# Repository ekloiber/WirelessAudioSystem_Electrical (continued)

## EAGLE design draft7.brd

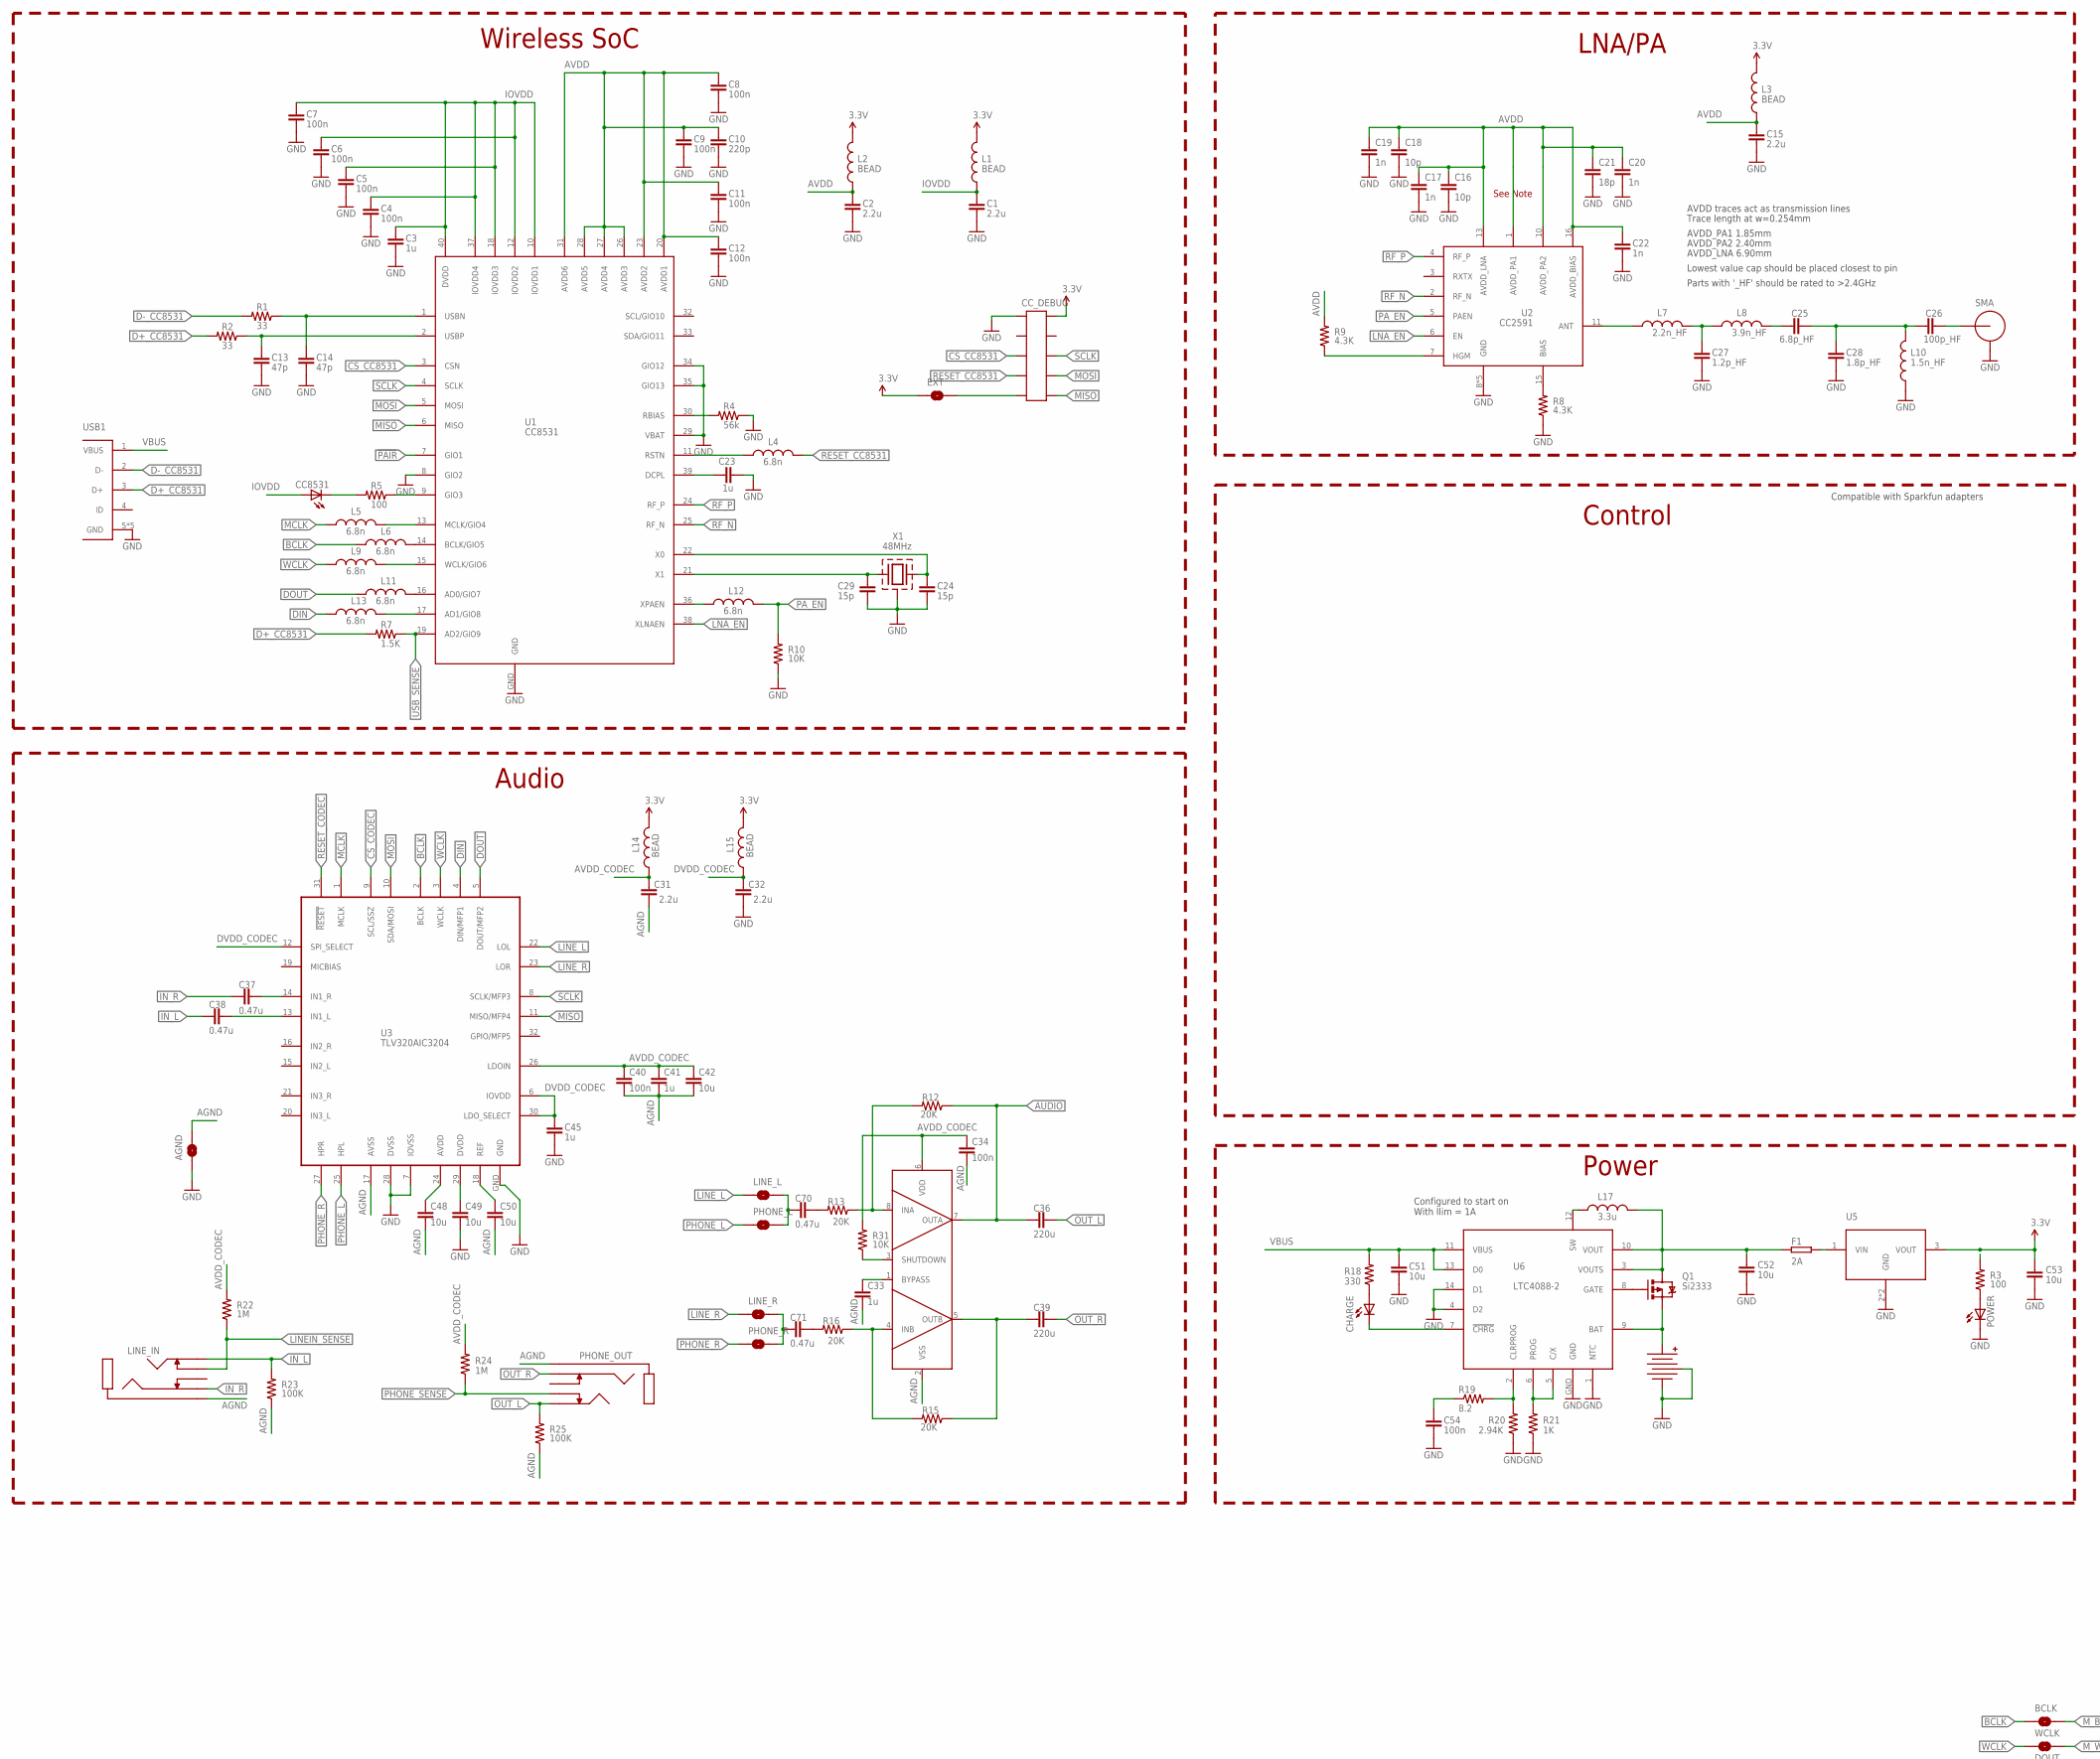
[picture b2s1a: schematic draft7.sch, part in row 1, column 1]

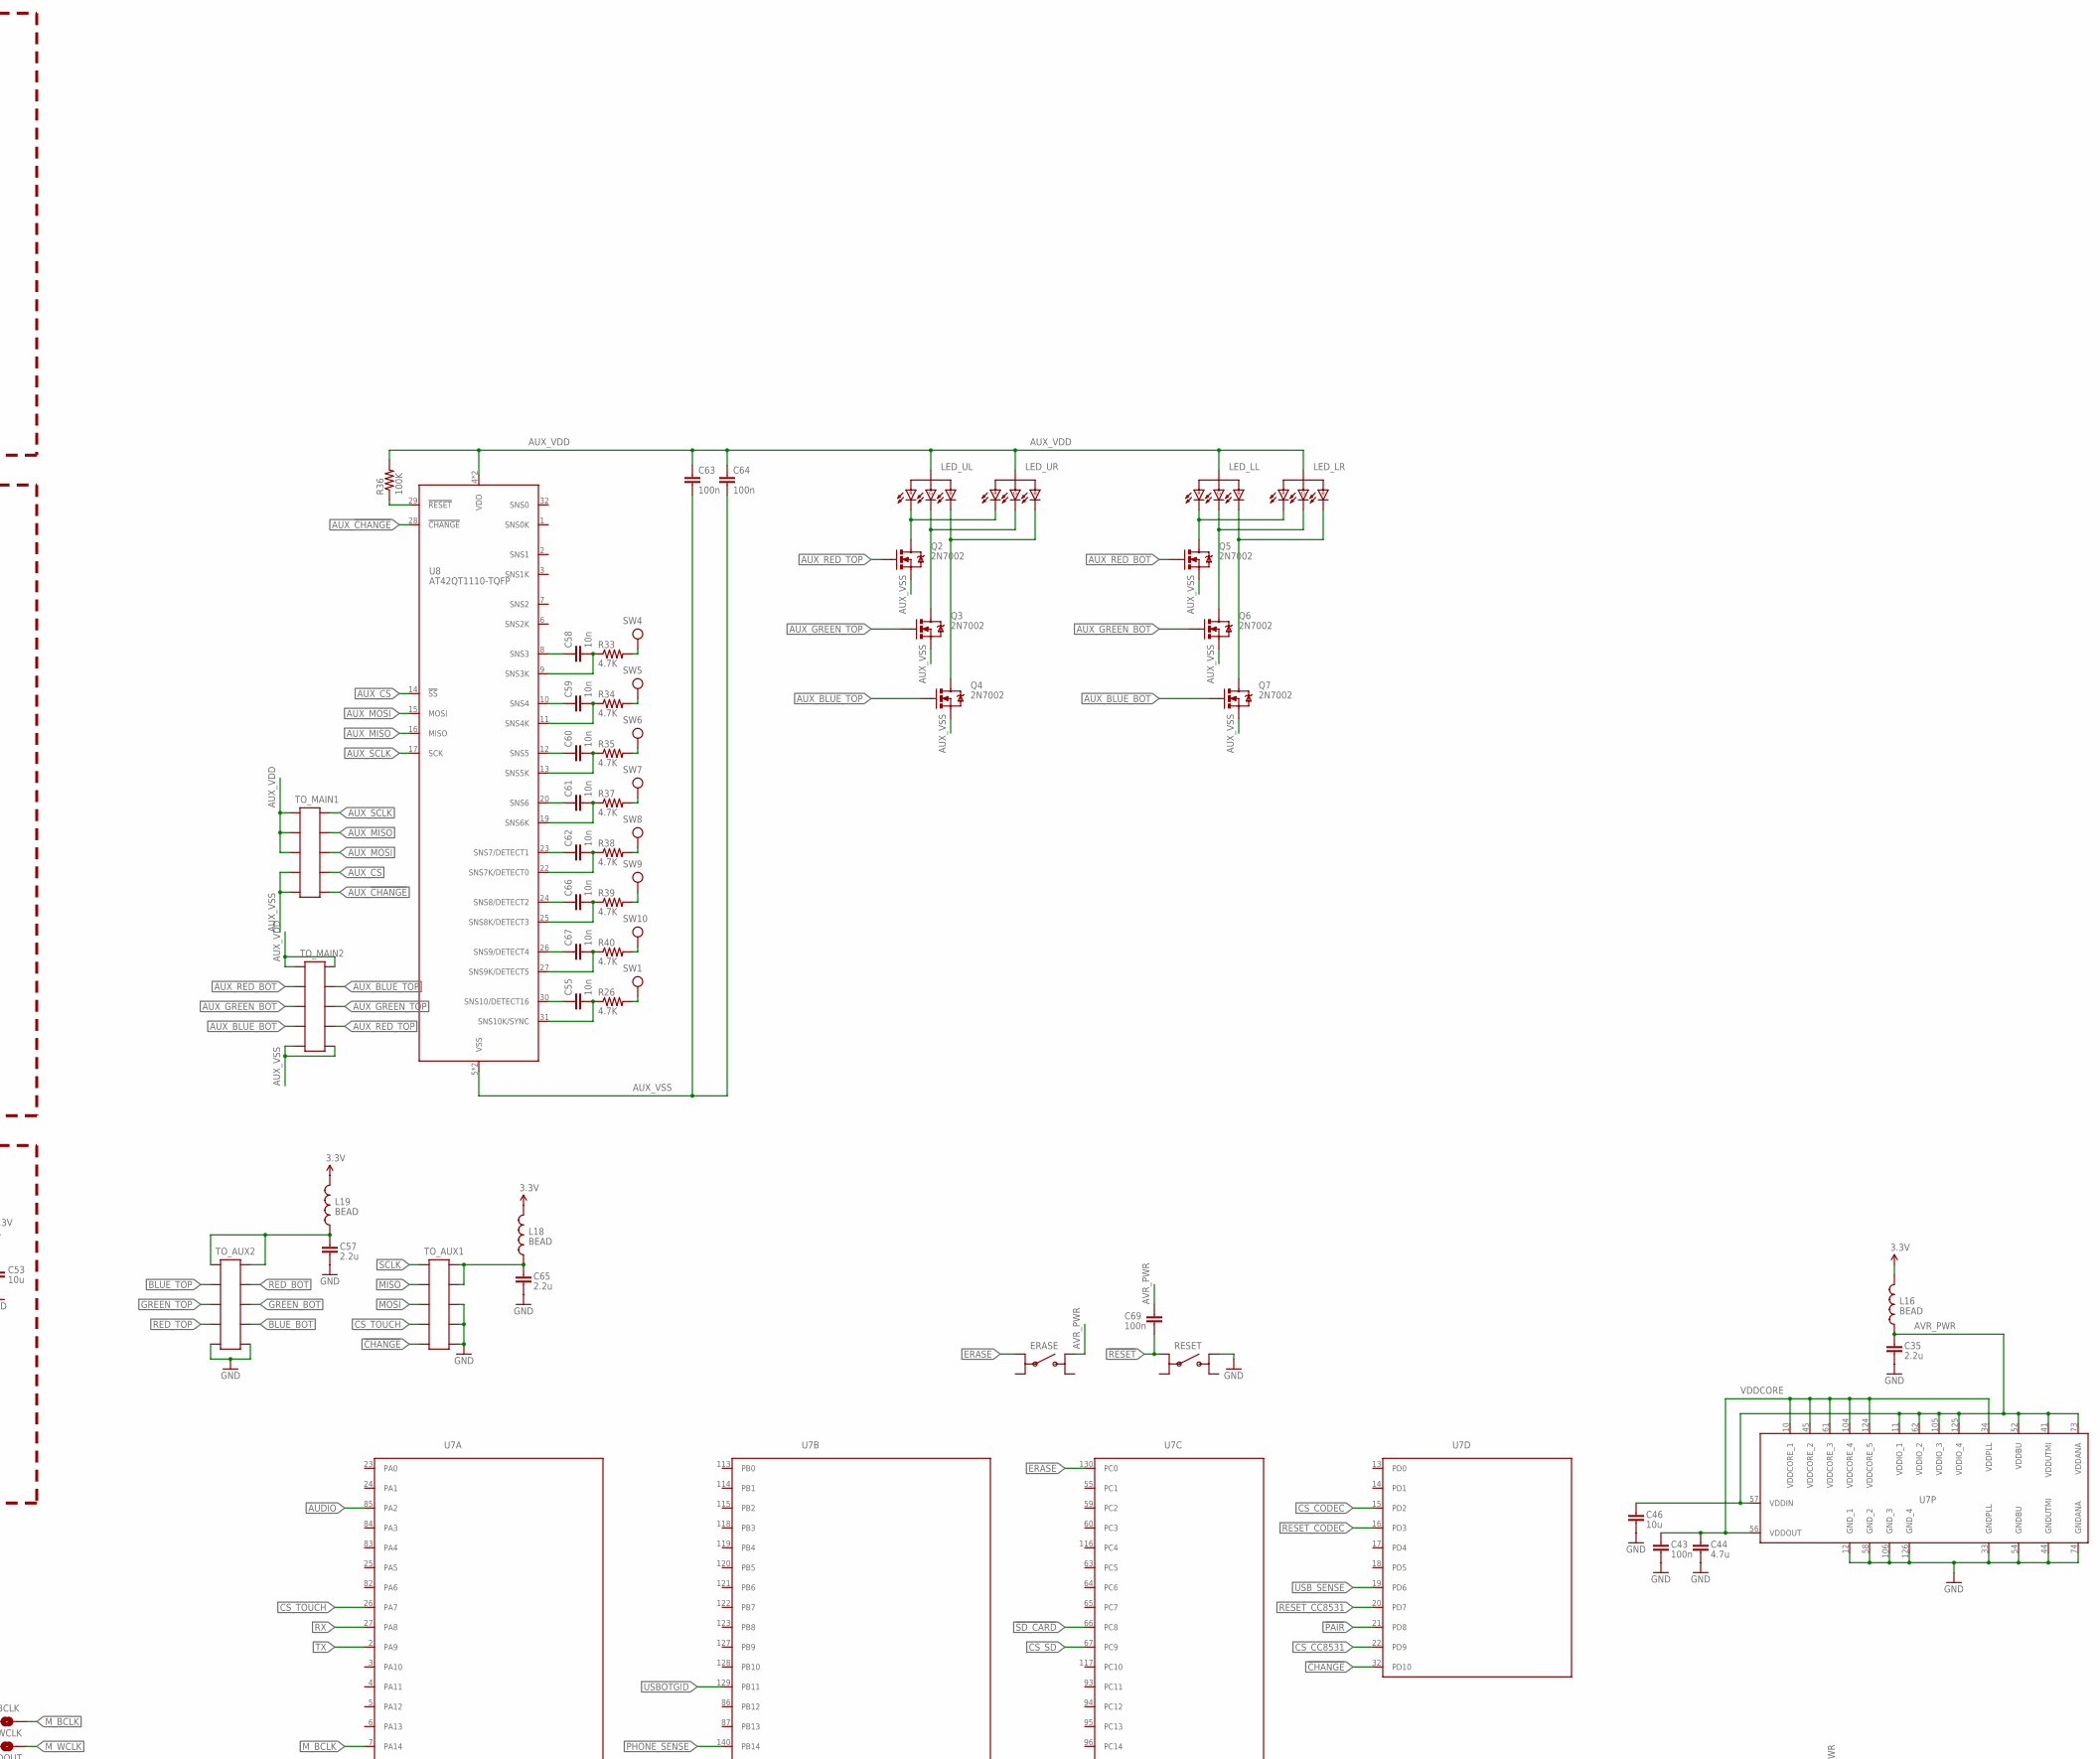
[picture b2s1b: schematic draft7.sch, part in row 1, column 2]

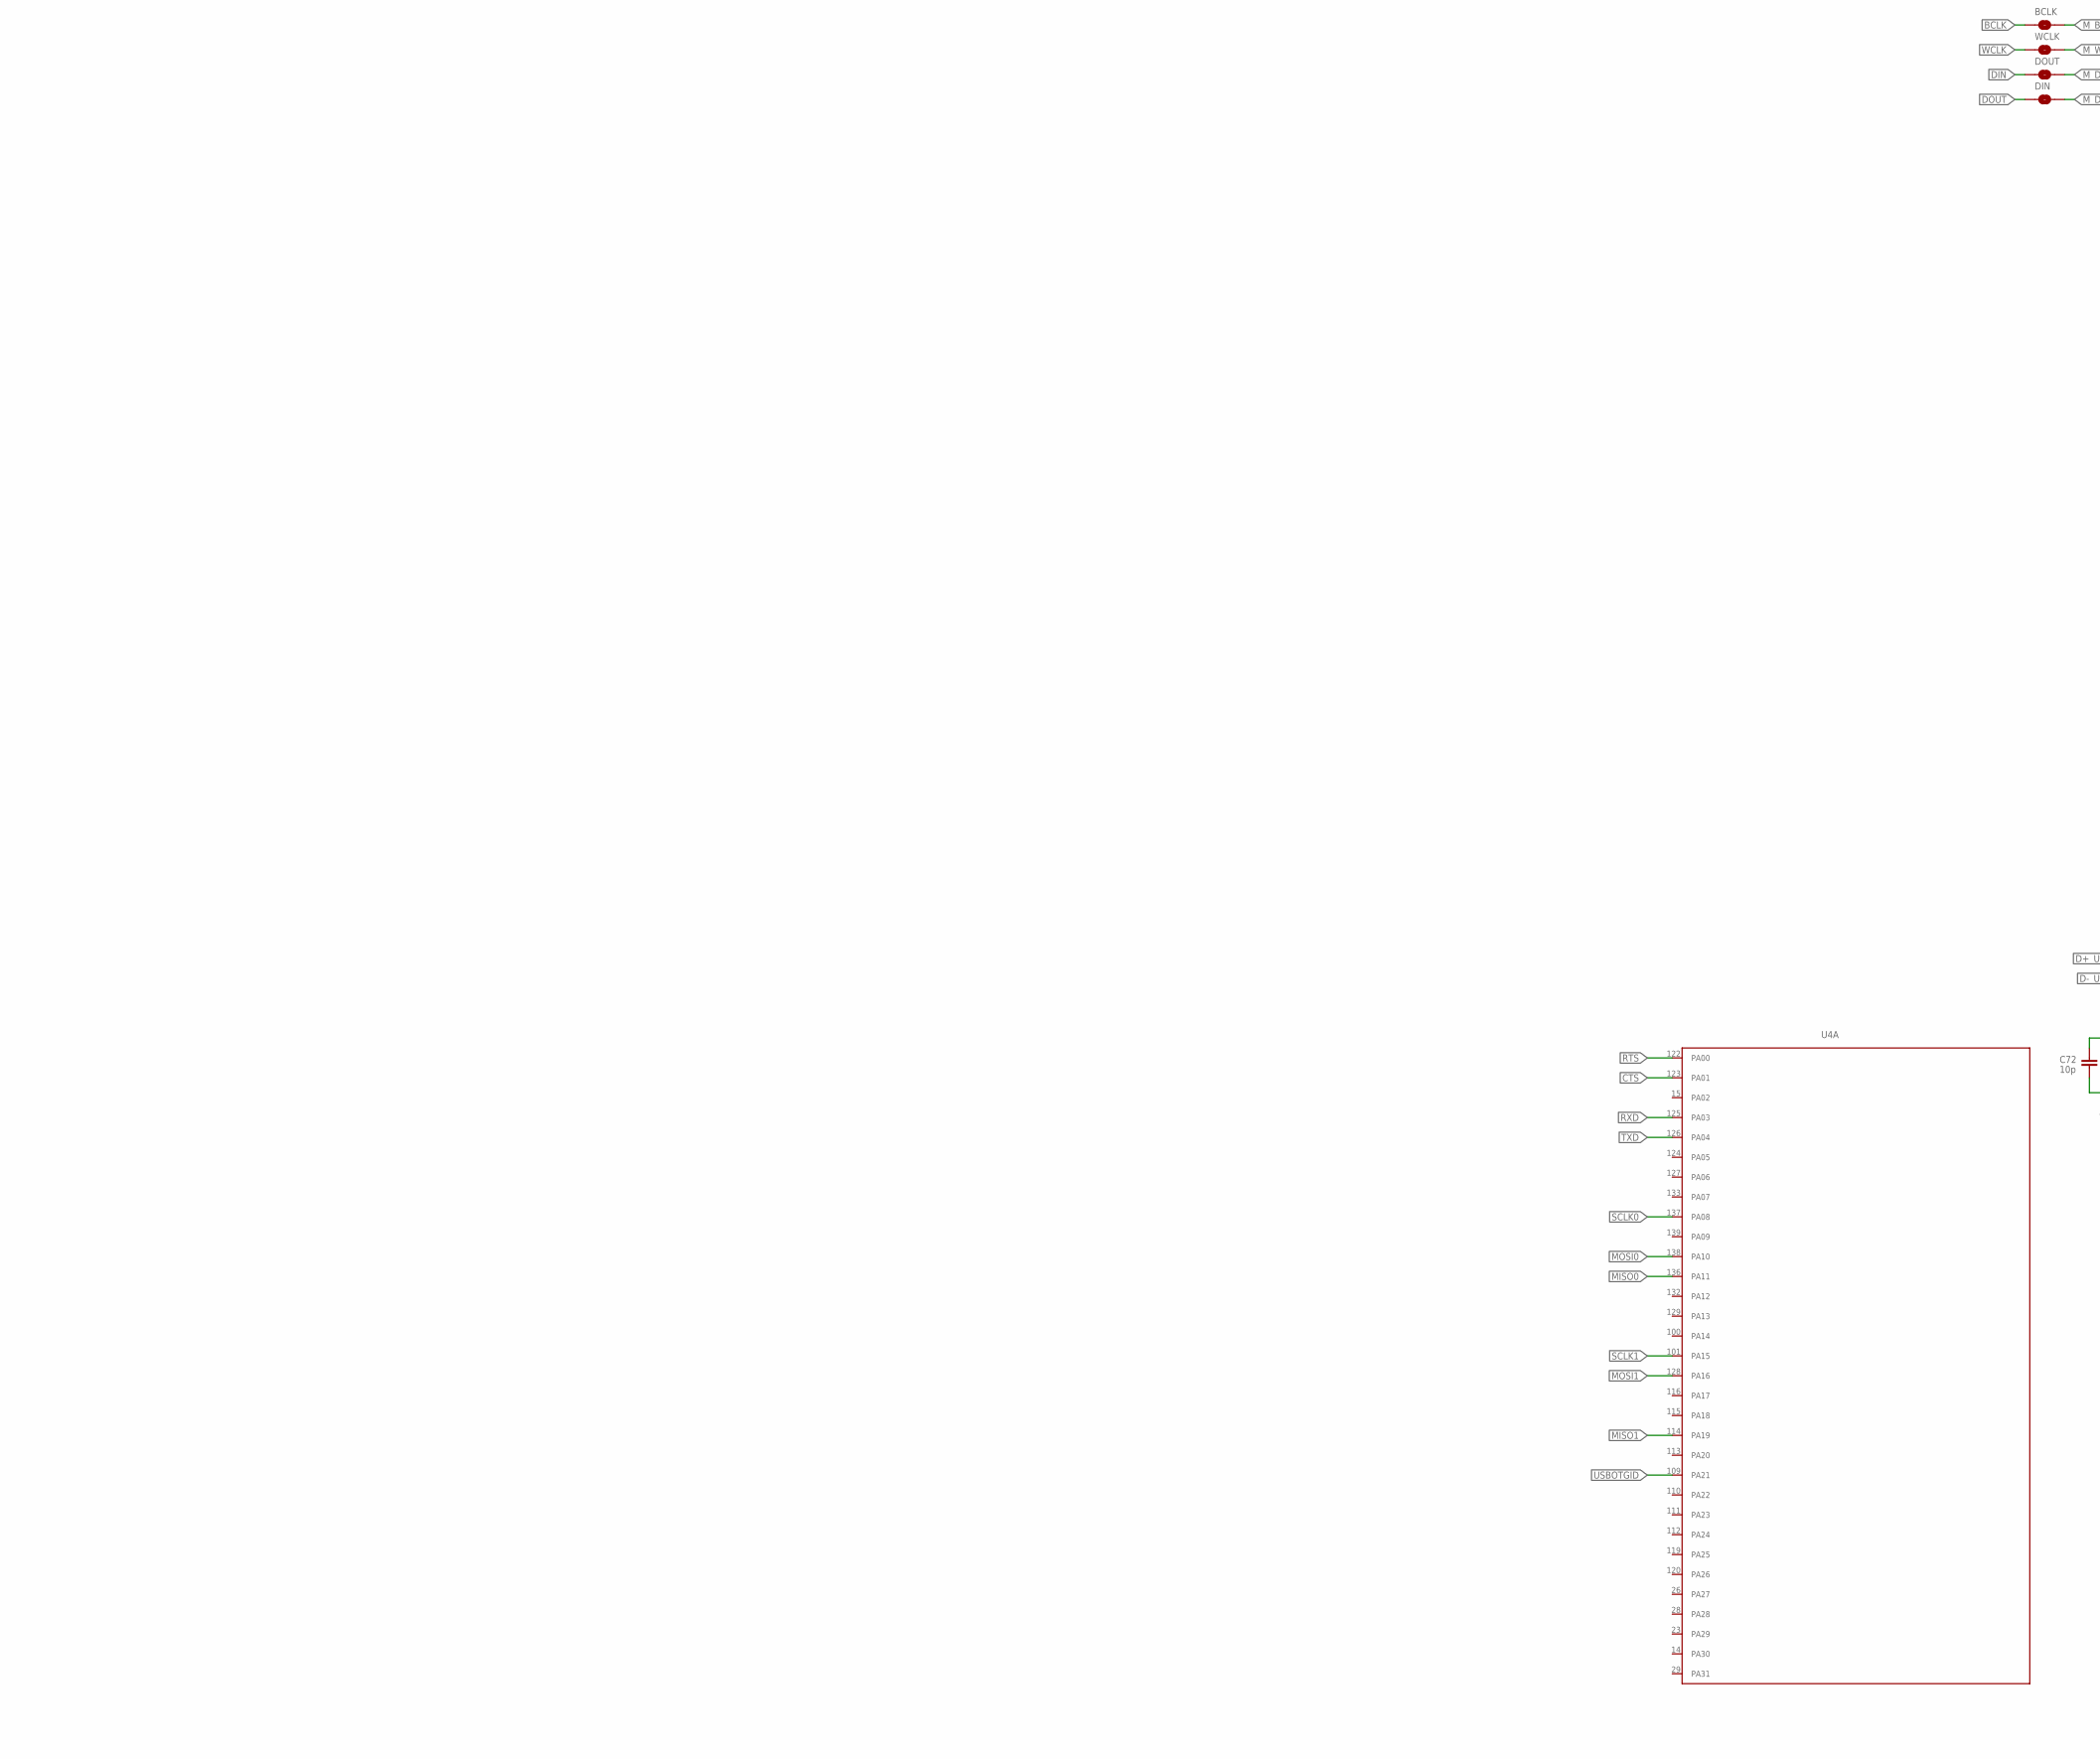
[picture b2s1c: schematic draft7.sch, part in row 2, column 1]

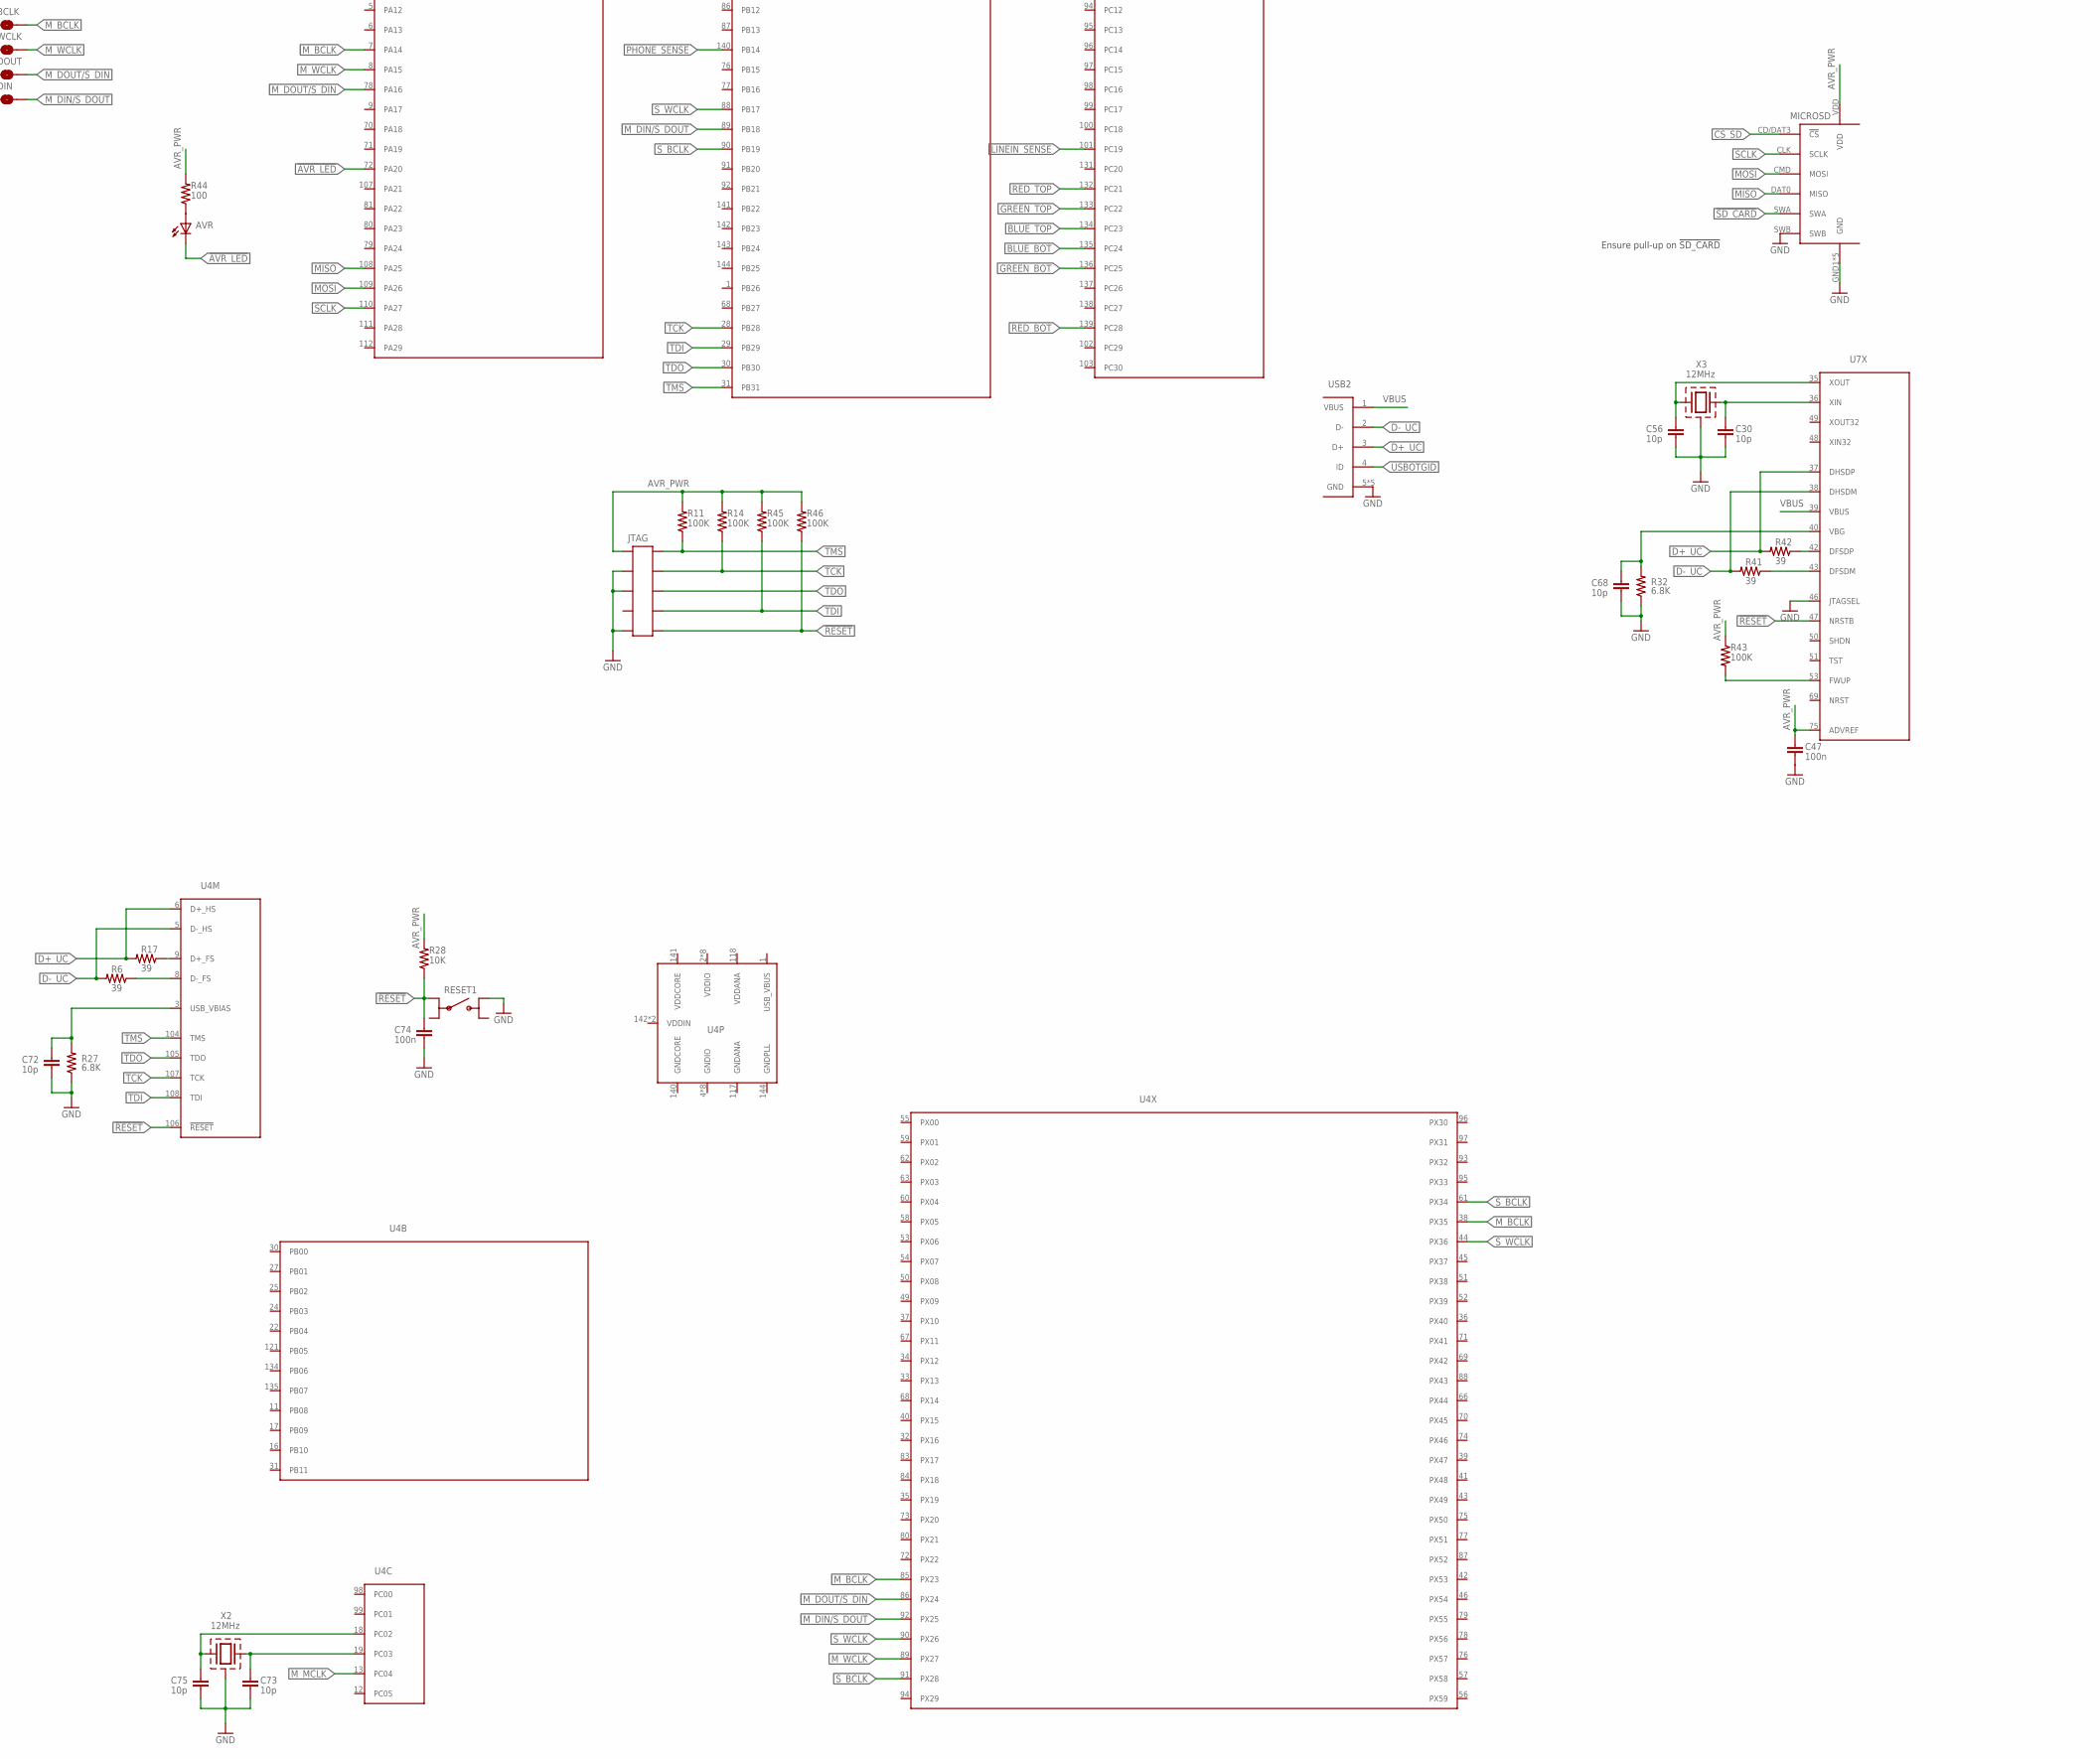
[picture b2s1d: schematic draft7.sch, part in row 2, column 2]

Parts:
AGND: SOLDERJUMPERNO; SJ_2S-NO
AVR: LED1206; LED-1206
BATTERY: BATTERY-LIPO-JST; 1775469-2
BCLK: SOLDERJUMPERNO; SJ_2S-NO
C1, C2, C15, C31, C32, C35, C57, C65: 2.2u; C0603
C3, C23, C33, C41, C45: 1u; C0603
C4, C5, C6, C7, C8, C9, C11, C12, C34, C40, C43, C47, C54, C63, C64, C69, C74: 100n; C0603
C10: 220p; C0603
C13, C14: 47p; C0603
C16, C18, C30, C56, C68, C72, C73, C75: 10p; C0603
C17, C19, C20, C22: 1n; C0603
C21: 18p; C0603
C24, C29: 15p; C0603
C25: 6.8p_HF; C0603
C26: 100p_HF; C0603
C27: 1.2p_HF; C0603
C28: 1.8p_HF; C0603
C36, C39: 220u; C1210
C37, C38, C70, C71: 0.47u; C0603
C42, C46, C48, C49, C50, C51, C52, C53: 10u; C0603
C44: 4.7u; C0603
C55, C58, C59, C60, C61, C62, C66, C67: 10n; C0603
CC8531: LED1206; LED-1206
CC_DEBUG: HEADER-10P-SMD-MALE2; HEADER-10P-1.27MM
CHARGE: LED1206; LED-1206
DIN: SOLDERJUMPERNO; SJ_2S-NO
DOUT: SOLDERJUMPERNO; SJ_2S-NO
ERASE: TACT_SWITCH-PTS-525; PTS-525
EXT: SOLDERJUMPERNO; SJ_2S-NO
F1: 2A; 1210
JTAG: HEADER-10P-SMD-MALE2; HEADER-10P-1.27MM
L1, L2, L3, L14, L15, L16, L18, L19: BEAD; 0603
L4, L5, L6, L9, L11, L12, L13: 6.8n; 0603
L7: 2.2n_HF; 0603
L8: 3.9n_HF; 0603
L10: 1.5n_HF; 0603
L17: 3.3u; IFSC-1111AB-01
LED_LL: LED_RGB; PLCC-4
LED_LR: LED_RGB; PLCC-4
LED_UL: LED_RGB; PLCC-4
LED_UR: LED_RGB; PLCC-4
LINE_IN: PHONE_SW-STX-35332-5N; STX-35332-5N
LINE_L: SOLDERJUMPERNO; SJ_2S-NO
LINE_R: SOLDERJUMPERNO; SJ_2S-NO
MICROSD: MICROSD104031-0811; MOLEX_104031-0811
PHONE_L: SOLDERJUMPERNO; SJ_2S-NO
PHONE_OUT: PHONE_SW-STX-35332-5N; STX-35332-5N
PHONE_R: SOLDERJUMPERNO; SJ_2S-NO
POWER: LED1206; LED-1206
Q1: Si2333; SOT23-3
Q2, Q3, Q4, Q5, Q6, Q7: 2N7002; SOT23-3
R1, R2: 33; R0603
R3, R5, R44: 100; R0603
R4: 56k; R0603
R6, R17, R41, R42: 39; R0603
R7: 1.5K; R0603
R8, R9: 4.3K; R0603
R10, R28, R31: 10K; R0603
R11, R14, R23, R25, R36, R43, R45, R46: 100K; R0603
R12, R13, R15, R16: 20K; R0603
R18: 330; R0603
R19: 8.2; R0603
R20: 2.94K; R0603
R21: 1K; R0603
R22, R24: 1M; R0603
R26, R33, R34, R35, R37, R38, R39, R40: 4.7K; R0603
R27, R32: 6.8K; R0603
RESET, RESET1: TACT_SWITCH-PTS-525; PTS-525
SMA: SMA-REVSMA-0.62; CONREVSMA003.062
SW1, SW4, SW5, SW6, SW7, SW8, SW9, SW10: TOUCH_PAD-CIRCLE-15MM; TOUCH-CIRCLE-15MM
TO_AUX1, TO_AUX2: HEADER-10P-SMD-2MM-FEMALE; M22-63405
TO_MAIN1, TO_MAIN2: HEADER-10P-SMD-2MM-MALE; M22-53205
U1: CC8531; S-PVQFN-N40
U2: CC2591; S-PVQFN-N16
U3: TLV320AIC3204; S-PVQFN-N32
U4: AT32UC3A3-LQFP-144; LQFP-144
U5: MCP1826-SOT223; SOT-223
U6: LTC4088-2; DFN-14
U7: ATSAM3X8E_ALT-LQFP-144; LQFP-144
U8: AT42QT1110-TQFP; S-PQFP-N32
U9: LM4881; SO08
USB1, USB2: USB_MICRO_AB
WCLK: SOLDERJUMPERNO; SJ_2S-NO
X1: 48MHz; ABM3C
X2, X3: 12MHz; ABM8G

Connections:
3.3V: C53.1, CC_DEBUG.2, EXT.1, L1.2, L2.2, L3.2, L14.2, L15.2, L16.2, L18.2, L19.2, R3.2, U5.3 (VOUT)
!AVR_LED: AVR.C, U7.72 (PA20)
!CHANGE: TO_AUX1.9, U7.32 (PD10)
!PAIR: U1.7 (GIO1), U7.21 (PD8)
!RESET: C69.2, C74.1, JTAG.10, R28.1, R46.1, RESET.1, RESET1.1, U4.106 (!RESET), U7.47 (NRSTB)
!SD_CARD: MICROSD.SWA, U7.66 (PC8)
AGND: AGND.2, C31.2, C33.2, C34.2, C40.2, C41.2, C42.2, C48.2, C50.2, LINE_IN.5 (GND), PHONE_OUT.5 (GND), R23.1, R25.1, U3.17 (AVSS), U9.2 (VSS)
AUDIO: C36.1, R12.1, U7.85 (PA2), U9.7 (OUTA)
AUX_!CHANGE: TO_MAIN1.10, U8.28 (!CHANGE)
AUX_BLUE_BOT: Q7.1 (G), TO_MAIN2.7
AUX_BLUE_TOP: Q4.1 (G), TO_MAIN2.4
AUX_CS: TO_MAIN1.8, U8.14 (!SS)
AUX_GREEN_BOT: Q6.1 (G), TO_MAIN2.5
AUX_GREEN_TOP: Q3.1 (G), TO_MAIN2.6
AUX_MISO: TO_MAIN1.4, U8.16 (MISO)
AUX_MOSI: TO_MAIN1.6, U8.15 (MOSI)
AUX_RED_BOT: Q5.1 (G), TO_MAIN2.3
AUX_RED_TOP: Q2.1 (G), TO_MAIN2.8
AUX_SCLK: TO_MAIN1.2, U8.17 (SCK)
AUX_VDD: C63.1, C64.1, LED_LL.2 (A), LED_LL.2-2 (A), LED_LR.2 (A), LED_LR.2-2 (A), LED_UL.2 (A), LED_UL.2-2 (A), LED_UR.2 (A), LED_UR.2-2 (A), R36.2, TO_MAIN1.1, TO_MAIN1.3, TO_MAIN1.5, TO_MAIN2.1, TO_MAIN2.2, U8.4 (VDD), U8.18 (VDD)
AUX_VSS: C63.2, C64.2, Q2.2 (S), Q3.2 (S), Q4.2 (S), Q5.2 (S), Q6.2 (S), Q7.2 (S), TO_MAIN1.7, TO_MAIN1.9, TO_MAIN2.9, TO_MAIN2.10, U8.5 (VSS), U8.21 (VSS)
AVDD: C2.1, C8.1, C9.1, C10.1, C11.1, C12.1, C15.1, C16.1, C17.1, C18.1, C19.1, C20.1, C21.1, C22.1, L2.1, L3.1, R9.2, U1.20 (AVDD1), U1.23 (AVDD2), U1.26 (AVDD3), U1.27 (AVDD4), U1.28 (AVDD5), U1.31 (AVDD6), U2.1 (AVDD_PA1), U2.10 (AVDD_PA2), U2.13 (AVDD_LNA), U2.16 (AVDD_BIAS)
AVDD_CODEC: C31.1, C34.1, C40.1, C41.1, C42.1, L14.1, R22.2, R24.2, R31.2, U3.26 (LDOIN), U9.6 (VDD)
AVR_PWR: C35.1, C46.1, C47.1, C69.1, ERASE.3, JTAG.1, L16.1, MICROSD.VDD, R11.2, R14.2, R28.2, R43.1, R44.2, R45.2, R46.2, U7.11 (VDDIO_1), U7.41 (VDDUTMI), U7.52 (VDDBU), U7.57 (VDDIN), U7.62 (VDDIO_2), U7.73 (VDDANA), U7.75 (ADVREF), U7.105 (VDDIO_3), U7.125 (VDDIO_4)
BAT: BATTERY.+, Q1.2 (S), U6.9 (BAT)
BCLK: BCLK.1, L6.1, U3.2 (BCLK)
BLUE_BOT: TO_AUX2.8, U7.135 (PC24)
BLUE_TOP: TO_AUX2.3, U7.134 (PC23)
CS_CC8531: CC_DEBUG.5, U1.3 (CSN), U7.22 (PD9)
CS_CODEC: U3.9 (SCL/SSZ), U7.15 (PD2)
CS_SD: MICROSD.CD/DAT3 (!CS), U7.67 (PC9)
CS_TOUCH: TO_AUX1.7, U7.26 (PA7)
CTS: U4.123 (PA01)
D+_CC8531: R2.2, R7.2, USB1.3 (D+)
D+_UC: R17.2, R42.2, U4.6 (D+_HS), U7.37 (DHSDP), USB2.3 (D+)
D-_CC8531: R1.2, USB1.2 (D-)
D-_UC: R6.2, R41.2, U4.5 (D-_HS), U7.38 (DHSDM), USB2.2 (D-)
DIN: DOUT.1, L13.1, U3.4 (DIN/MFP1)
DOUT: DIN.1, L11.1, U3.5 (DOUT/MFP2)
DVDD: C49.1, U3.29 (DVDD)
DVDD_CODEC: C32.1, C45.1, L15.1, U3.6 (IOVDD), U3.12 (SPI_SELECT), U3.30 (LDO_SELECT)
ERASE: ERASE.1, U7.130 (PC0)
GND: AGND.1, BATTERY.- (N), BATTERY.X1 (CASE), BATTERY.X2 (CASE), C1.2, C2.2, C3.2, C4.2, C5.2, C6.2, C7.2, C8.2, C9.2, C10.2, C11.2, C12.2, C13.2, C14.2, C15.2, C16.2, C17.2, C18.2, C19.2, C20.2, C21.2, C22.2, C23.2, C24.2, C27.2, C28.2, C29.2, C30.2, C32.2, C35.2, C43.2, C44.2, C45.2, C46.2, C47.2, C49.2, C51.2, C52.2, C53.2, C54.2, C56.2, C57.2, C65.2, C68.2, C72.2, C73.2, C74.2, C75.2, CC_DEBUG.1, JTAG.3, JTAG.5, JTAG.9, L10.1, MICROSD.GND1 (GND), MICROSD.GND2 (GND), MICROSD.GND3 (GND), MICROSD.GND4 (GND), MICROSD.SWB, MICROSD.VSS (GND), POWER.C, R4.1, R8.1, R10.1, R20.1, R21.1, R27.1, R32.1, RESET.3, RESET1.3, SMA.GND1 (GND), SMA.GND2 (GND), SMA.GND3 (GND), SMA.GND4 (GND), TO_AUX1.6, TO_AUX1.8, TO_AUX1.10, TO_AUX2.9, TO_AUX2.10, U1.8 (GIO2), U1.29 (VBAT), U1.34 (GIO12), U1.35 (GIO13), U1.GND, U2.8 (GND), U2.9 (GND), U2.12 (GND), U2.14 (GND), U2.GND, U3.7 (IOVSS), U3.28 (DVSS), U3.GND, U5.2 (GND), U5.4 (GND), U6.1 (NTC), U6.4 (D2), U6.14 (D1), U6.GND, U7.12 (GND_1), U7.33 (GNDPLL), U7.44 (GNDUTMI), U7.46 (JTAGSEL), U7.54 (GNDBU), U7.58 (GND_2), U7.74 (GNDANA), U7.106 (GND_3), U7.126 (GND_4), USB1.5 (GND), USB1.GND1 (GND), USB1.GND2 (GND), USB1.GND3 (GND), USB1.GND4 (GND), USB2.5 (GND), USB2.GND1 (GND), USB2.GND2 (GND), USB2.GND3 (GND), USB2.GND4 (GND), X1.2 (CASE), X1.4 (CASE), X2.GND-1 (CASE), X2.GND-2 (CASE), X3.GND-1 (CASE), X3.GND-2 (CASE)
GREEN_BOT: TO_AUX2.6, U7.136 (PC25)
GREEN_TOP: TO_AUX2.5, U7.133 (PC22)
IN_L: C38.1, LINE_IN.4 (L), R23.2
IN_R: C37.1, LINE_IN.1 (R)
IOVDD: C1.1, C3.1, C4.1, C5.1, C6.1, C7.1, CC8531.A, L1.1, U1.10 (IOVDD1), U1.12 (IOVDD2), U1.18 (IOVDD3), U1.37 (IOVDD4), U1.40 (DVDD)
IOVDD1: C14.1, R1.1, U1.1 (USBN)
IOVDD2: C13.1, R2.1, U1.2 (USBP)
LINEIN_SENSE: LINE_IN.3 (L_SW), R22.1, U7.101 (PC19)
LINE_L: LINE_L.1, U3.22 (LOL)
LINE_R: LINE_R.1, U3.23 (LOR)
LNA_EN: U1.38 (XLNAEN), U2.6 (EN)
MCLK: L5.1, U3.1 (MCLK)
MISO: CC_DEBUG.10, MICROSD.DAT0 (MISO), TO_AUX1.3, U1.6 (MISO), U3.11 (MISO/MFP4), U7.108 (PA25)
MISO0: U4.136 (PA11)
MISO1: U4.114 (PA19)
MOSI: CC_DEBUG.8, MICROSD.CMD (MOSI), TO_AUX1.5, U1.5 (MOSI), U3.10 (SDA/MOSI), U7.109 (PA26)
MOSI0: U4.138 (PA10)
MOSI1: U4.128 (PA16)
M_BCLK: BCLK.2, U4.38 (PX35), U4.85 (PX23), U7.7 (PA14)
M_DIN/S_DOUT: DIN.2, U4.92 (PX25), U7.89 (PB18)
M_DOUT/S_DIN: DOUT.2, U4.86 (PX24), U7.78 (PA16)
M_MCLK: U4.13 (PC04)
M_WCLK: U4.89 (PX27), U7.8 (PA15), WCLK.2
unnamed: C29.1, U1.21 (X1), X1.1
unnamed: C24.1, U1.22 (X0), X1.3 (2)
unnamed: L4.1, U1.11 (RSTN)
unnamed: L11.2, U1.16 (AD0/GIO7)
unnamed: L6.2, U1.14 (BCLK/GIO5)
unnamed: C56.1, U7.35 (XOUT), X3.X1 (1)
unnamed: R8.2, U2.15 (BIAS)
unnamed: R9.1, U2.7 (HGM)
unnamed: C26.2, SMA.SIG
unnamed: C55.2, R26.1, U8.31 (SNS10K/SYNC)
unnamed: C55.1, U8.30 (SNS10/DETECT16)
unnamed: AVR.A, R44.1
unnamed: L7.1, U2.11 (ANT)
unnamed: C27.1, L7.2, L8.1
unnamed: C25.1, L8.2
unnamed: C25.2, C26.1, C28.1, L10.2
unnamed: C48.1, U3.24 (AVDD)
unnamed: L12.1, U1.36 (XPAEN)
unnamed: R4.2, U1.30 (RBIAS)
unnamed: C70.2, R13.2
unnamed: C23.1, U1.39 (DCPL)
unnamed: F1.2, U5.1 (VIN)
unnamed: L5.2, U1.13 (MCLK/GIO4)
unnamed: C71.2, R16.2
unnamed: L9.2, U1.15 (WCLK/GIO6)
unnamed: C33.1, U9.1 (BYPASS)
unnamed: L13.2, U1.17 (AD1/GIO8)
unnamed: R5.1, U1.9 (GIO3)
unnamed: CC8531.C, R5.2
unnamed: C58.2, R33.1, U8.9 (SNS3K)
unnamed: POWER.A, R3.1
unnamed: CHARGE.C, U6.7 (!CHRG)
unnamed: CHARGE.A, R18.1
unnamed: C37.2, U3.14 (IN1_R)
unnamed: C38.2, U3.13 (IN1_L)
unnamed: L17.1, U6.12 (SW)
unnamed: R21.2, U6.5 (C/X), U6.6 (PROG)
unnamed: R19.2, R20.2, U6.2 (CLRPROG)
unnamed: R6.1, U4.8 (D-_FS)
unnamed: C39.1, R15.1, U9.5 (OUTB)
unnamed: C59.2, R34.1, U8.11 (SNS4K)
unnamed: C60.2, R35.1, U8.13 (SNS5K)
unnamed: C70.1, LINE_L.2, PHONE_L.2
unnamed: R26.2, SW1.P$1
unnamed: C71.1, LINE_R.2, PHONE_R.2
unnamed: R17.1, U4.9 (D+_FS)
unnamed: C72.1, R27.2, U4.3 (USB_VBIAS)
unnamed: C54.1, R19.1
unnamed: C52.1, F1.1, L17.2, Q1.3 (D), U6.3 (VOUTS), U6.10 (VOUT)
unnamed: CC_DEBUG.9, EXT.2
unnamed: Q1.1 (G), U6.8 (GATE)
unnamed: C75.1, U4.18 (PC02), X2.X1 (1)
unnamed: R12.2, R13.1, U9.8 (INA)
unnamed: R15.2, R16.1, U9.4 (INB)
unnamed: R31.1, U9.3 (SHUTDOWN)
unnamed: LED_UL.1 (KR), LED_UL.1-2 (KR), LED_UR.1 (KR), LED_UR.1-2 (KR), Q2.3 (D)
unnamed: C73.1, U4.19 (PC03), X2.X2 (2)
unnamed: LED_UL.4 (KG), LED_UL.4-2 (KG), LED_UR.4 (KG), LED_UR.4-2 (KG), Q3.3 (D)
unnamed: C30.1, U7.36 (XIN), X3.X2 (2)
unnamed: C58.1, U8.8 (SNS3)
unnamed: R33.2, SW4.P$1
unnamed: C59.1, U8.10 (SNS4)
unnamed: R34.2, SW5.P$1
unnamed: C60.1, U8.12 (SNS5)
unnamed: R35.2, SW6.P$1
unnamed: C66.2, R39.1, U8.25 (SNS8K/DETECT3)
unnamed: C57.1, L19.1, TO_AUX2.1, TO_AUX2.2
unnamed: C67.2, R40.1, U8.27 (SNS9K/DETECT5)
unnamed: C66.1, U8.24 (SNS8/DETECT2)
unnamed: R39.2, SW9.P$1
unnamed: C61.2, R37.1, U8.19 (SNS6K)
unnamed: R37.2, SW7.P$1
unnamed: C62.2, R38.1, U8.22 (SNS7K/DETECT0)
unnamed: R38.2, SW8.P$1
unnamed: C62.1, U8.23 (SNS7/DETECT1)
unnamed: C61.1, U8.20 (SNS6)
unnamed: R36.1, U8.29 (!RESET)
unnamed: LED_UL.3 (KB), LED_UL.3-2 (KB), LED_UR.3 (KB), LED_UR.3-2 (KB), Q4.3 (D)
unnamed: LED_LL.1 (KR), LED_LL.1-2 (KR), LED_LR.1 (KR), LED_LR.1-2 (KR), Q5.3 (D)
unnamed: LED_LL.4 (KG), LED_LL.4-2 (KG), LED_LR.4 (KG), LED_LR.4-2 (KG), Q6.3 (D)
unnamed: C67.1, U8.26 (SNS9/DETECT4)
unnamed: R40.2, SW10.P$1
unnamed: LED_LL.3 (KB), LED_LL.3-2 (KB), LED_LR.3 (KB), LED_LR.3-2 (KB), Q7.3 (D)
unnamed: C65.1, L18.1, TO_AUX1.2, TO_AUX1.4
unnamed: R41.1, U7.43 (DFSDM)
unnamed: R42.1, U7.42 (DFSDP)
unnamed: C68.1, R32.2, U7.40 (VBG)
unnamed: R43.2, U7.53 (FWUP)
OUT_L: C36.2, PHONE_OUT.4 (L), R25.2
OUT_R: C39.2, PHONE_OUT.1 (R)
PA_EN: L12.2, R10.2, U2.5 (PAEN)
PHONE_L: PHONE_L.1, U3.25 (HPL)
PHONE_R: PHONE_R.1, U3.27 (HPR)
PHONE_SENSE: PHONE_OUT.3 (L_SW), R24.1, U7.140 (PB14)
RED_BOT: TO_AUX2.4, U7.139 (PC28)
RED_TOP: TO_AUX2.7, U7.132 (PC21)
REF: C50.1, U3.18 (REF)
RESET_CC8531: CC_DEBUG.7, L4.2, U7.20 (PD7)
RESET_CODEC: U3.31 (!RESET), U7.16 (PD3)
RF_N: U1.25 (RF_N), U2.2 (RF_N)
RF_P: U1.24 (RF_P), U2.4 (RF_P)
RTS: U4.122 (PA00)
RX: U7.27 (PA8)
RXD: U4.125 (PA03)
SCLK: CC_DEBUG.6, MICROSD.CLK (SCLK), TO_AUX1.1, U1.4 (SCLK), U3.8 (SCLK/MFP3), U7.110 (PA27)
SCLK0: U4.137 (PA08)
SCLK1: U4.101 (PA15)
S_BCLK: U4.61 (PX34), U4.91 (PX28), U7.90 (PB19)
S_WCLK: U4.44 (PX36), U4.90 (PX26), U7.88 (PB17)
TCK: JTAG.4, R14.1, U4.107 (TCK), U7.28 (PB28)
TDI: JTAG.8, R45.1, U4.108 (TDI), U7.29 (PB29)
TDO: JTAG.6, U4.105 (TDO), U7.30 (PB30)
TMS: JTAG.2, R11.1, U4.104 (TMS), U7.31 (PB31)
TX: U7.2 (PA9)
TXD: U4.126 (PA04)
USBOTGID: U4.109 (PA21), U7.129 (PB11), USB2.4 (ID)
USB_SENSE: R7.1, U1.19 (AD2/GIO9), U7.19 (PD6)
VBUS: C51.1, R18.2, U6.11 (VBUS), U6.13 (D0), U7.39 (VBUS), USB1.1 (VBUS), USB2.1 (VBUS)
VDDCORE: C43.1, C44.1, U7.10 (VDDCORE_1), U7.34 (VDDPLL), U7.45 (VDDCORE_2), U7.56 (VDDOUT), U7.61 (VDDCORE_3), U7.104 (VDDCORE_4), U7.124 (VDDCORE_5)
WCLK: L9.1, U3.3 (WCLK), WCLK.1

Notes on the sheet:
See Note
Compatible with Sparkfun adapters
AVDD_PA1 1.85mm
AVDD_PA2 2.40mm
AVDD_LNA 6.90mm
Trace length at w=0.254mm
Configured to start on With Ilim = 1A
Audio
Power
Control
AVDD traces act as transmission lines
Lowest value cap should be placed closest to pin
Parts with '_HF' should be rated to >2.4GHz
Wireless SoC
LNA/PA
Ensure pull-up on !SD_CARD
